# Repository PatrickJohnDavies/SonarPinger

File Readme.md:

# Intro
FPGA based single channel sonar.

# Release Notes:
* V0

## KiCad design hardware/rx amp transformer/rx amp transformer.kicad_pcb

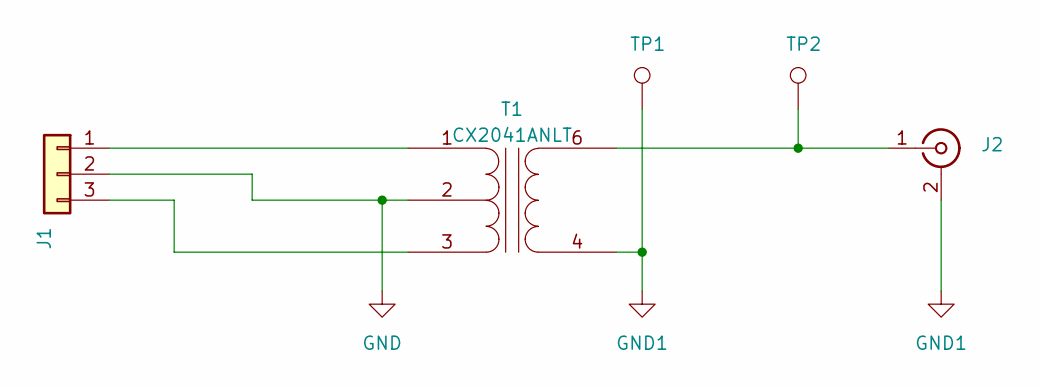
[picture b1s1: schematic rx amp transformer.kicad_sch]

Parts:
J1: Conn_01x03; PinHeader_1x03_P2.54mm_Vertical
J2: Conn_Coaxial; BNC_Molex_0731000105_Horizontal
T1: CX2041ANLT
TP1, TP2: TestPoint; TestPoint_THTPad_D1.8mm_Drill1.2mm

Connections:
GND: J1.2, T1.2 (SC)
GND1: J2.2 (Ext), T1.4 (AA), TP1.1
unnamed: J1.1, T1.1 (SA)
unnamed: J1.3, T1.3 (SB)
unnamed: J2.1 (In), T1.6 (AB), TP2.1

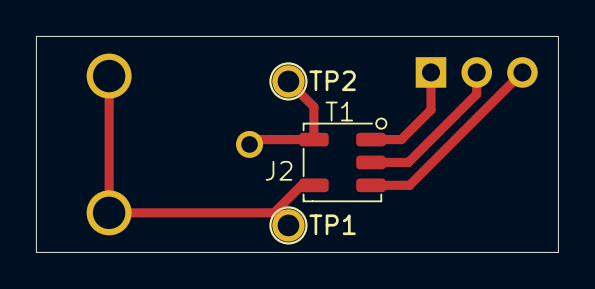
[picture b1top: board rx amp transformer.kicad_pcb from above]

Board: 2 copper layers, 29.0 x 12.0 mm, 5 parts (1 on the bottom side), 5 nets.

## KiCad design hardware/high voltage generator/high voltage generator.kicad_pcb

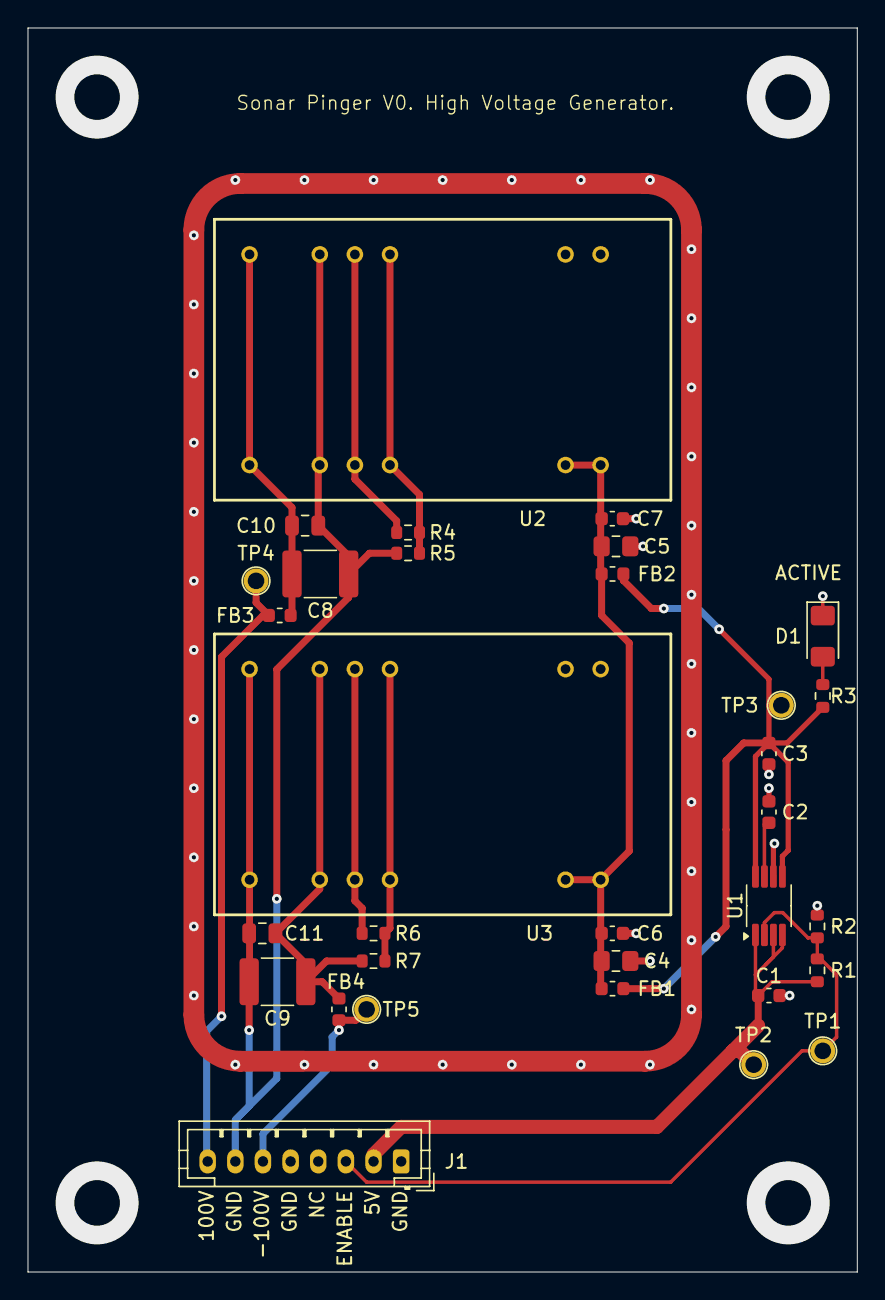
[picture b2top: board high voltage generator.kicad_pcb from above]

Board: 2 copper layers, 60.0 x 90.0 mm, 34 parts (1 on the bottom side), 16 nets.

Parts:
C1, C3, C6, C7: 0.1u; C_0603_1608Metric
C2: 1n; C_0603_1608Metric
C4, C5: 10u; C_0805_2012Metric_Pad1.18x1.45mm_HandSolder
C8, C9: 1u; C_1812_4532Metric
C10, C11: 10n; C_0805_2012Metric
D1: LED; LED_1206_3216Metric_Pad1.42x1.75mm_HandSolder
FB1, FB2, FB3, FB4: FerriteBead; L_0603_1608Metric
J1: Conn_01x08; JST_PH_B8B-PH-K_1x08_P2.00mm_Vertical
J2: RFShield_TwoPieces; Shield_MS638-10F
NT1: NetTie_2; NetTie-2_SMD_Pad0.5mm
R1, R2: 10K; R_0603_1608Metric
R3: 120; R_0603_1608Metric
R4, R6: 1.5k; R_0603_1608Metric
R5, R7: 3.6k; R_0603_1608Metric
TP1, TP2, TP3, TP4, TP5: TestPoint; TestPoint_THTPad_D1.8mm_Drill1.2mm
U1: TPS22958; VSSOP-8_3x3mm_P0.65mm
U2, U3: R05-100B; Converter_DCDC_RECOM_RXX-B

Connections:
+5V: C1.1, J1.2, R1.2, TP2.1, U1.1 (VIN), U1.3 (VBIAS), U1.4 (VIN)
+VIN: C4.1, C5.1, C6.1, C7.1, FB1.2, FB2.2, U2.22 (+VIN), U2.23 (+VIN), U3.22 (+VIN), U3.23 (+VIN)
/100V: FB3.2, J1.8, TP4.1
/+VO: C8.2, C10.2, FB3.1, U2.12 (+VOUT), U2.13 (+VOUT)
/-100V: FB4.2, J1.6, TP5.1
/-VO: C9.1, C11.1, FB4.1, R7.2, U3.10 (-VOUT), U3.15 (-VOUT)
/ENABLE: J1.3, R1.1, R2.2, TP1.1, U1.2 (ON)
GND: C1.2, C2.2, C3.2, C4.2, C5.2, C6.2, C7.2, D1.1 (K), J1.1, J1.5, J1.7, J2.1 (Shield), NT1.1, R2.1, U1.6 (GND), U2.2 (-VIN), U2.3 (-VIN), U3.2 (-VIN), U3.3 (-VIN)
GND1: C8.1, C9.2, C10.1, C11.2, NT1.2, R5.2, U2.10 (-VOUT), U2.15 (-VOUT), U3.12 (+VOUT), U3.13 (+VOUT)
unnamed: D1.2 (A), R3.1
unnamed: R4.1, U2.9 (VREF), U2.16 (VREF)
unnamed: R4.2, R5.1, U2.8 (VADJ), U2.17 (VADJ)
unnamed: R6.1, U3.9 (VREF), U3.16 (VREF)
unnamed: R6.2, R7.1, U3.8 (VADJ), U3.17 (VADJ)
unnamed: C2.1, U1.7 (CT)
VDC: C3.1, FB1.1, FB2.1, R3.2, TP3.1, U1.5 (VOUT), U1.8 (VOUT)

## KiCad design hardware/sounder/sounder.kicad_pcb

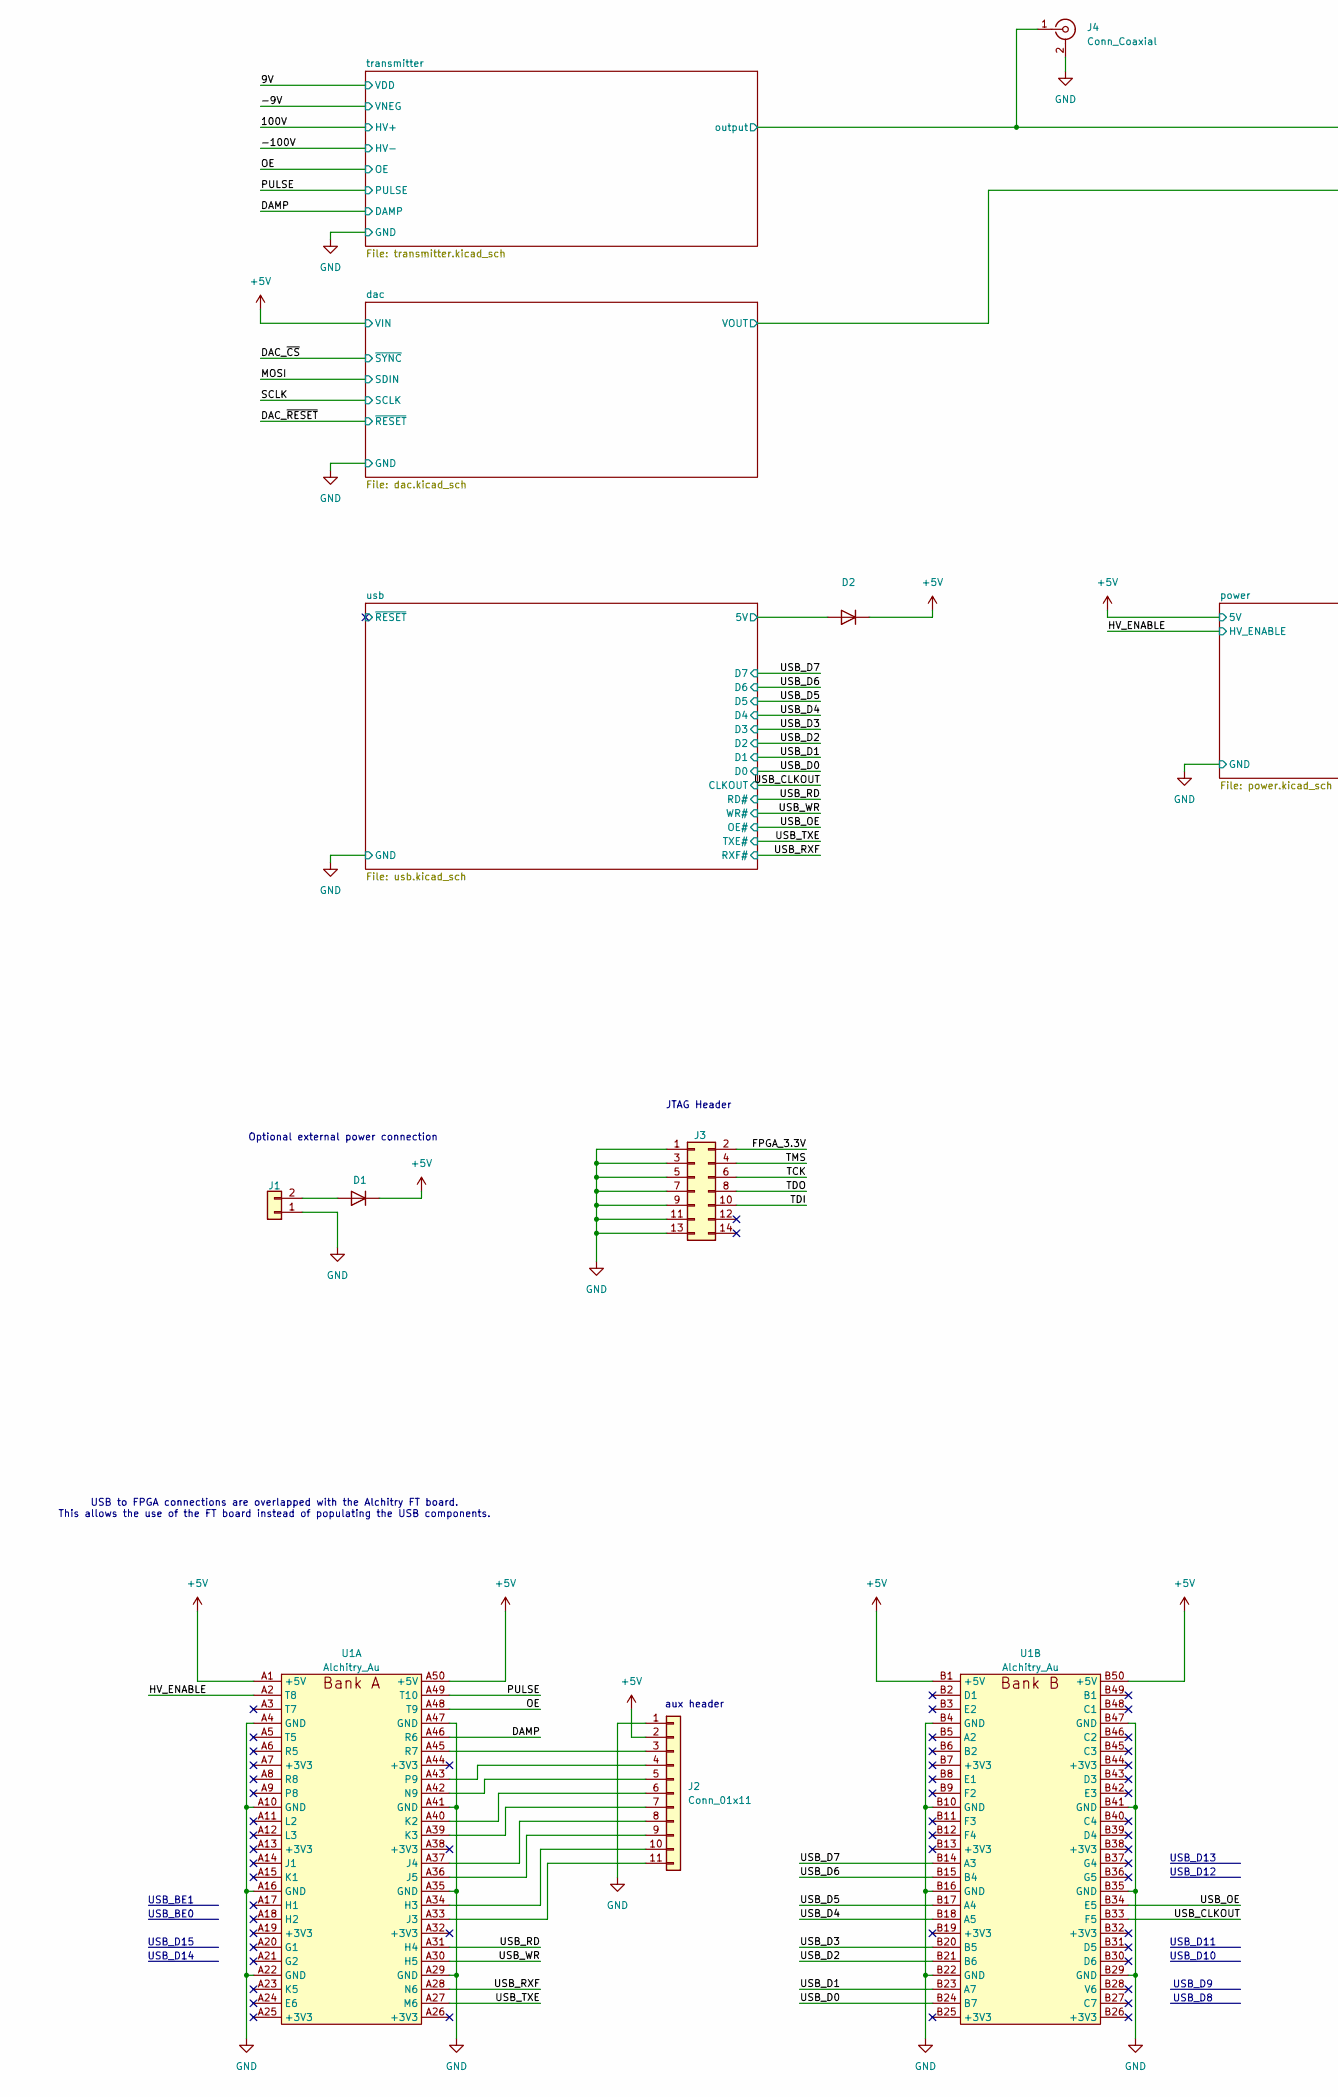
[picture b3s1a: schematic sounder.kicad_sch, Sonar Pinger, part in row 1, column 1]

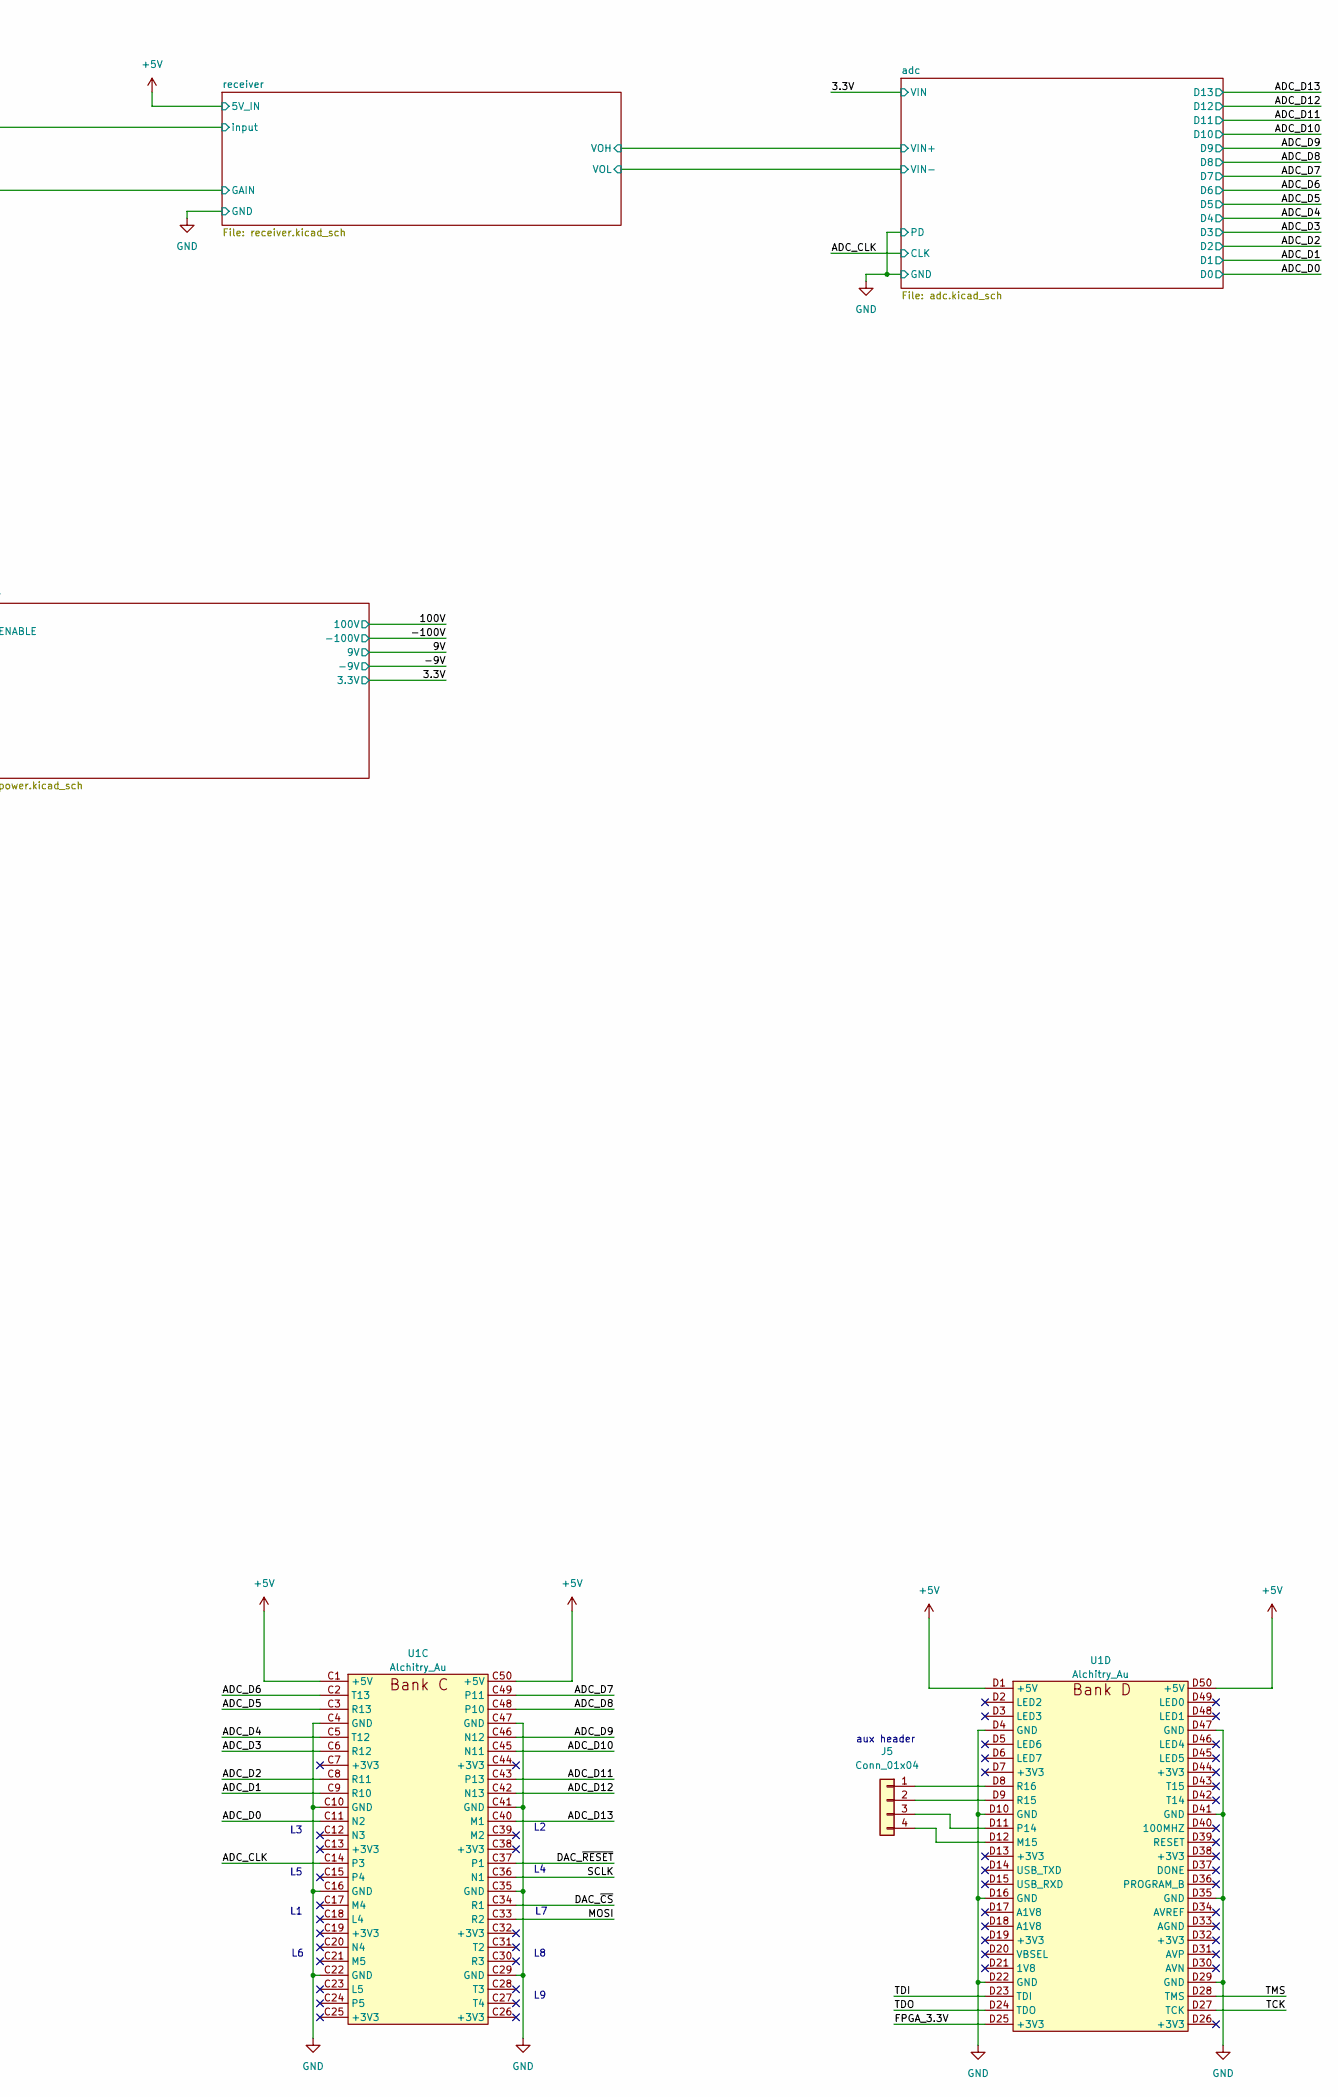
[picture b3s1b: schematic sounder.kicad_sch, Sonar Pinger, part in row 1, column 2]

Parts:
D1, D2: D; D_SOD-123F
J1: Conn_01x02; JST_PH_B2B-PH-K_1x02_P2.00mm_Vertical
J2: Conn_01x11; PinHeader_1x11_P2.54mm_Vertical
J3: Conn_02x07_Odd_Even; PinHeader_2x07_P2.54mm_Vertical
J4: Conn_Coaxial; RF2-04A-T-00-50-G
J5: Conn_01x04; PinHeader_1x04_P2.54mm_Vertical
U1: Alchitry_Au

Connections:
+5V: D1.1 (K), D2.1 (K), J2.2, U1.A1 (+5V), U1.A50 (+5V), U1.B1 (+5V), U1.B50 (+5V), U1.C1 (+5V), U1.C50 (+5V), U1.D1 (+5V), U1.D50 (+5V); also elsewhere on the board
/ADC_CLK: U1.C14 (P3); also elsewhere on the board
/ADC_D0: U1.C11 (N2); also elsewhere on the board
/ADC_D1: U1.C9 (R10); also elsewhere on the board
/ADC_D2: U1.C8 (R11); also elsewhere on the board
/ADC_D3: U1.C6 (R12); also elsewhere on the board
/ADC_D4: U1.C5 (T12); also elsewhere on the board
/ADC_D5: U1.C3 (R13); also elsewhere on the board
/ADC_D6: U1.C2 (T13); also elsewhere on the board
/ADC_D7: U1.C49 (P11); also elsewhere on the board
/ADC_D8: U1.C48 (P10); also elsewhere on the board
/ADC_D9: U1.C46 (N12); also elsewhere on the board
/ADC_D10: U1.C45 (N11); also elsewhere on the board
/ADC_D11: U1.C43 (P13); also elsewhere on the board
/ADC_D12: U1.C42 (N13); also elsewhere on the board
/ADC_D13: U1.C40 (M1); also elsewhere on the board
/DAC_~CS: U1.C34 (R1); also elsewhere on the board
/DAC_~RESET: U1.C37 (P1); also elsewhere on the board
/DAMP: U1.A46 (R6); also elsewhere on the board
/FPGA_3.3V: J3.2, U1.D25 (+3V3)
/HV_ENABLE: U1.A2 (T8); also elsewhere on the board
/MOSI: U1.C33 (R2); also elsewhere on the board
/OE: U1.A48 (T9); also elsewhere on the board
/PULSE: U1.A49 (T10); also elsewhere on the board
/SCLK: U1.C36 (N1); also elsewhere on the board
/TCK: J3.6, U1.D27 (TCK)
/TDI: J3.10, U1.D23 (TDI)
/TDO: J3.8, U1.D24 (TDO)
/TMS: J3.4, U1.D28 (TMS)
/USB_CLKOUT: U1.B33 (F5); also elsewhere on the board
/USB_D0: U1.B24 (B7); also elsewhere on the board
/USB_D1: U1.B23 (A7); also elsewhere on the board
/USB_D2: U1.B21 (B6); also elsewhere on the board
/USB_D3: U1.B20 (B5); also elsewhere on the board
/USB_D4: U1.B18 (A5); also elsewhere on the board
/USB_D5: U1.B17 (A4); also elsewhere on the board
/USB_D6: U1.B15 (B4); also elsewhere on the board
/USB_D7: U1.B14 (A3); also elsewhere on the board
/USB_OE: U1.B34 (E5); also elsewhere on the board
/USB_RD: U1.A31 (H4); also elsewhere on the board
/USB_RXF: U1.A28 (N6); also elsewhere on the board
/USB_TXE: U1.A27 (M6); also elsewhere on the board
/USB_WR: U1.A30 (H5); also elsewhere on the board
/receiver/input: J4.1 (In); also elsewhere on the board
/usb/5V: D2.2 (A); also elsewhere on the board
GND: J1.1, J2.1, J3.1, J3.3, J3.5, J3.7, J3.9, J3.11, J3.13, J4.2 (Ext), U1.A4 (GND), U1.A10 (GND), U1.A16 (GND), U1.A22 (GND), U1.A29 (GND), U1.A35 (GND), U1.A41 (GND), U1.A47 (GND), U1.B4 (GND), U1.B10 (GND), U1.B16 (GND), U1.B22 (GND), U1.B29 (GND), U1.B35 (GND), U1.B41 (GND), U1.B47 (GND), U1.C4 (GND), U1.C10 (GND), U1.C16 (GND), U1.C22 (GND), U1.C29 (GND), U1.C35 (GND), U1.C41 (GND), U1.C47 (GND), U1.D4 (GND), U1.D10 (GND), U1.D16 (GND), U1.D22 (GND), U1.D29 (GND), U1.D35 (GND), U1.D41 (GND), U1.D47 (GND); also elsewhere on the board
unnamed: D1.2 (A), J1.2
unnamed: J2.3, U1.A45 (R7)
unnamed: J2.4, U1.A43 (P9)
unnamed: J2.5, U1.A42 (N9)
unnamed: J2.6, U1.A40 (K2)
unnamed: J2.7, U1.A39 (K3)
unnamed: J2.8, U1.A37 (J4)
unnamed: J2.9, U1.A36 (J5)
unnamed: J2.10, U1.A34 (H3)
unnamed: J2.11, U1.A33 (J3)
unnamed: J5.1, U1.D8 (R16)
unnamed: J5.2, U1.D9 (R15)
unnamed: J5.3, U1.D11 (P14)
unnamed: J5.4, U1.D12 (M15)

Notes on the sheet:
Optional external power connection
USB_D12
JTAG Header
USB_BE1
aux header
USB_D15
USB_D10
USB_D8
USB to FPGA connections are overlapped with the Alchitry FT board. This allows the use of the FT board instead of populating the USB components.
USB_BE0
USB_D13
USB_D9
USB_D14
USB_D11

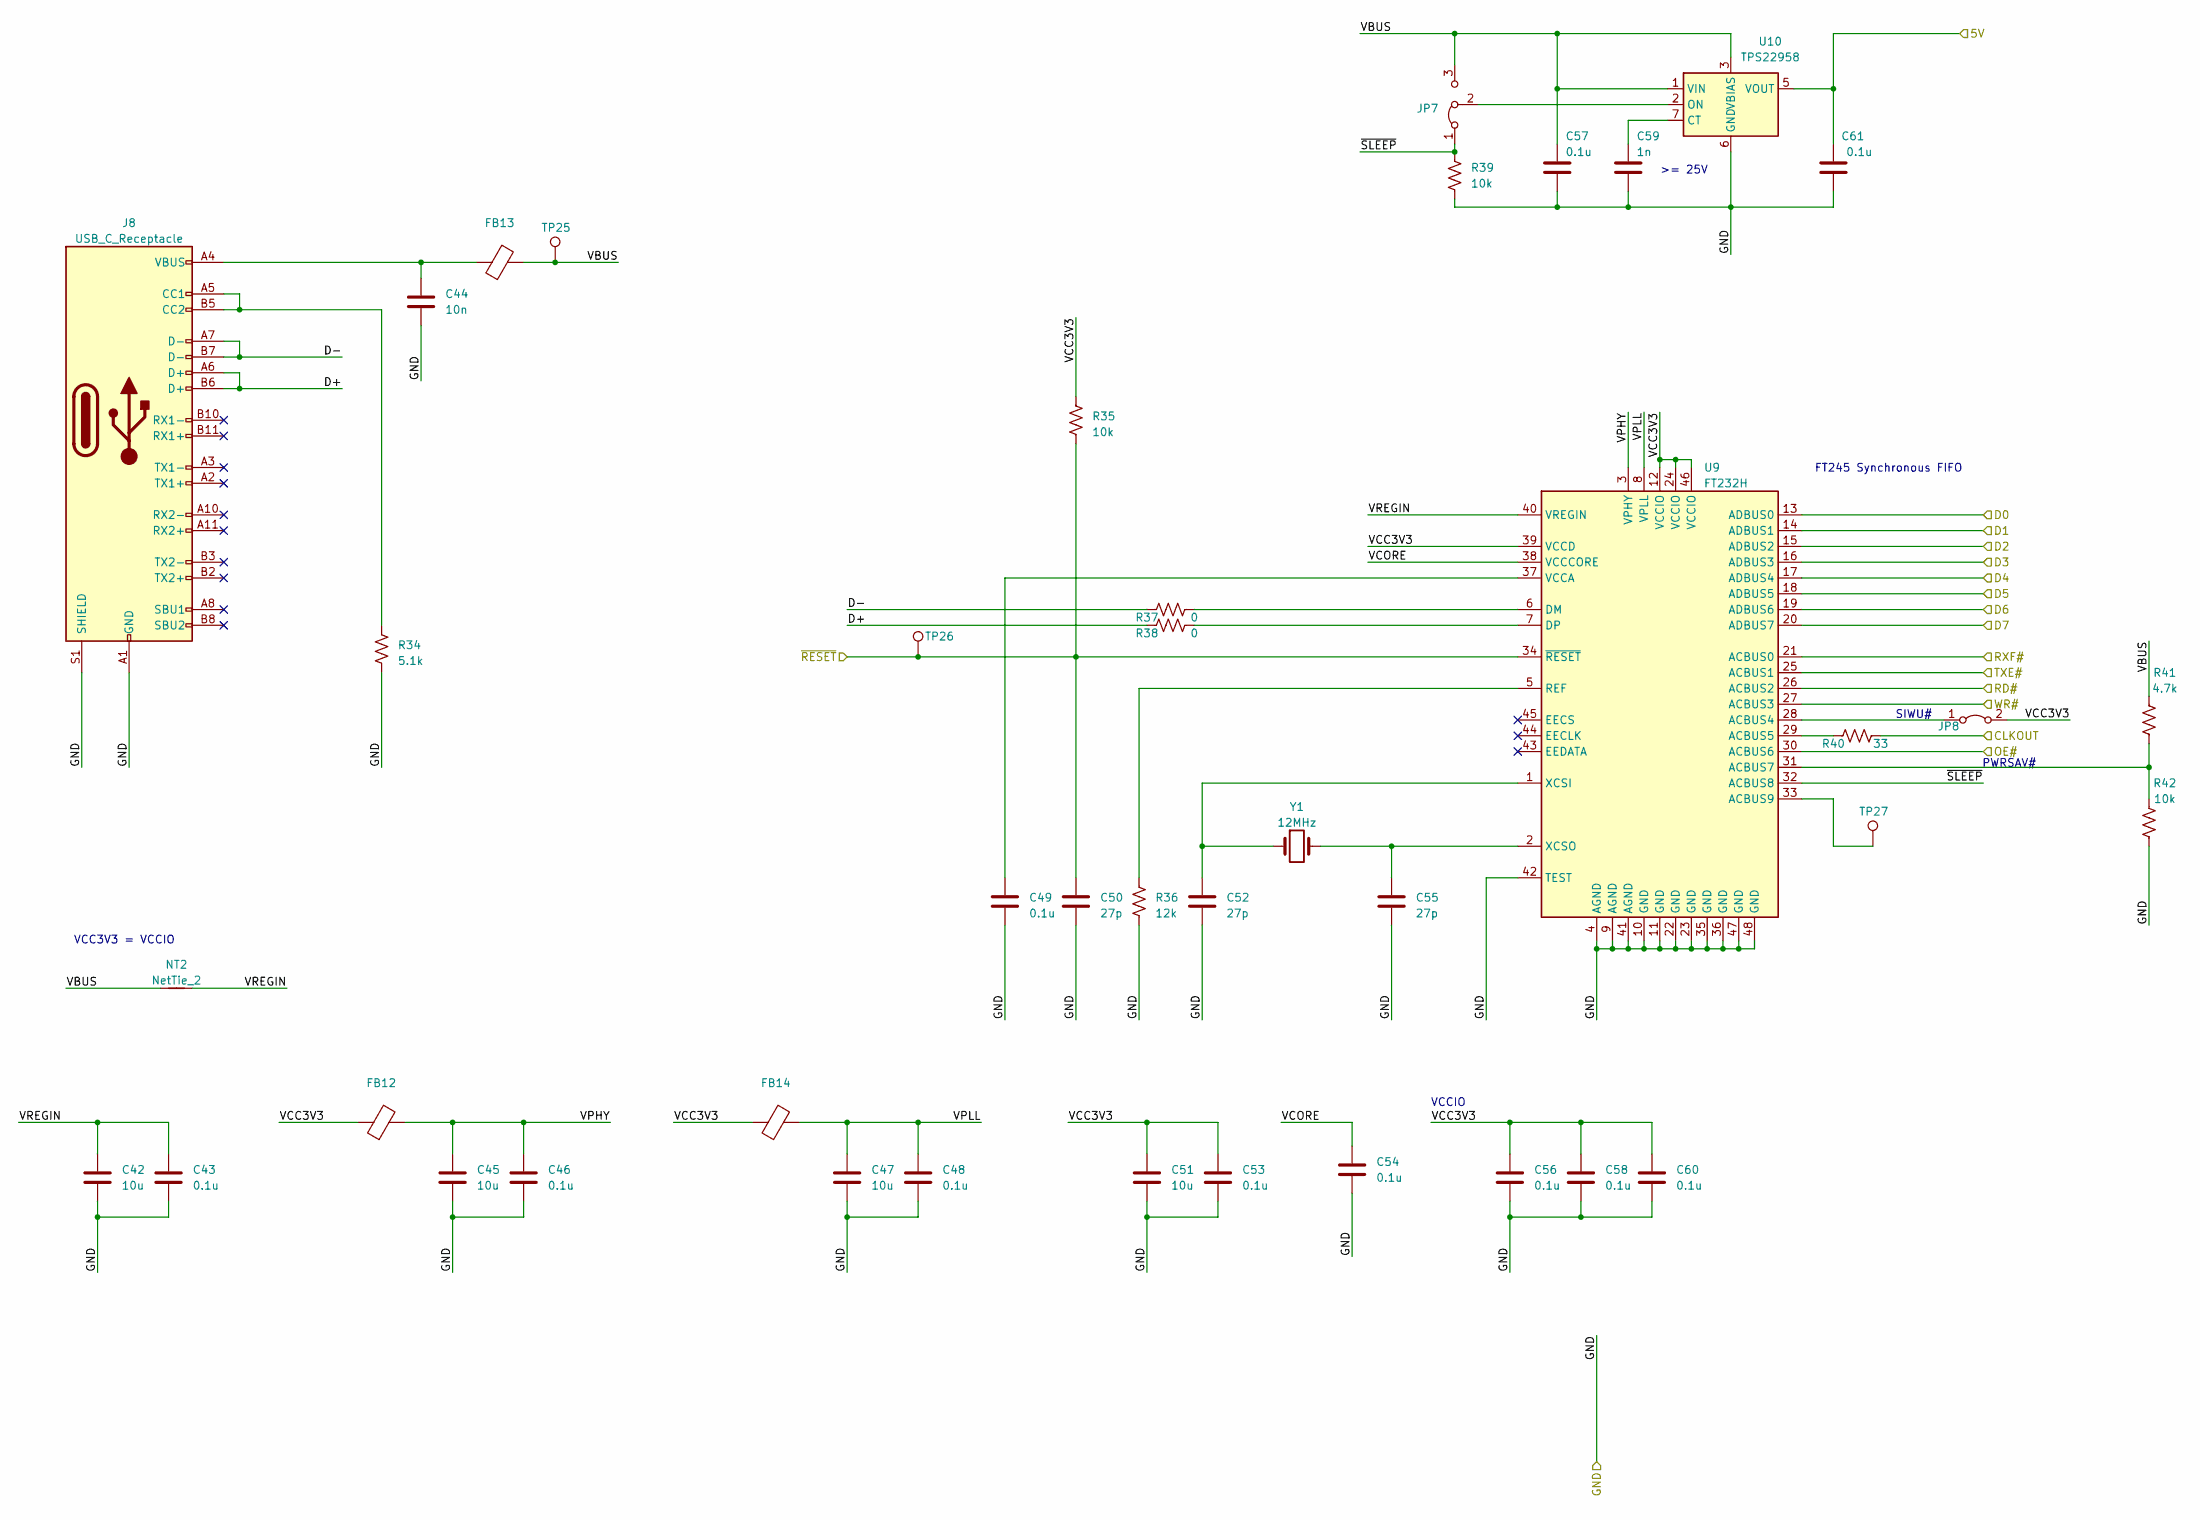
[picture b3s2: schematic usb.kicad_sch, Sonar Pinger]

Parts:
C42, C45, C47, C51: 10u; C_0805_2012Metric_Pad1.18x1.45mm_HandSolder
C43, C46, C48, C49, C53, C54, C56, C57, C58, C60, C61: 0.1u; C_0603_1608Metric
C44: 10n; C_0603_1608Metric
C50, C52, C55: 27p; C_0603_1608Metric
C59: 1n; C_0603_1608Metric
FB12, FB13, FB14: FerriteBead; L_0603_1608Metric
J8: USB_C_Receptacle; USB_C_Receptacle_Amphenol_12401548E4-2A_CircularHoles
JP7: Jumper_3_Bridged12; SolderJumper-3_P1.3mm_Bridged12_RoundedPad1.0x1.5mm
JP8: Jumper_2_Bridged; SolderJumper-2_P1.3mm_Bridged_RoundedPad1.0x1.5mm
NT2: NetTie_2; NetTie-2_SMD_Pad0.5mm
R34: 5.1k; R_0603_1608Metric
R35, R39, R42: 10k; R_0603_1608Metric
R36: 12k; R_0603_1608Metric
R37, R38: 0; R_0603_1608Metric
R40: 33; R_0603_1608Metric
R41: 4.7k; R_0603_1608Metric
TP25, TP26, TP27: TestPoint; TestPoint_THTPad_D1.8mm_Drill1.2mm
U9: FT232H; LQFP-48_7x7mm_P0.5mm
U10: TPS22958; VSSOP-8_3x3mm_P0.65mm
Y1: 12MHz; Crystal_SMD_HC49-SD_HandSoldering

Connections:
/USB_CLKOUT: R40.2; also elsewhere on the board
/USB_D0: U9.13 (ADBUS0); also elsewhere on the board
/USB_D1: U9.14 (ADBUS1); also elsewhere on the board
/USB_D2: U9.15 (ADBUS2); also elsewhere on the board
/USB_D3: U9.16 (ADBUS3); also elsewhere on the board
/USB_D4: U9.17 (ADBUS4); also elsewhere on the board
/USB_D5: U9.18 (ADBUS5); also elsewhere on the board
/USB_D6: U9.19 (ADBUS6); also elsewhere on the board
/USB_D7: U9.20 (ADBUS7); also elsewhere on the board
/USB_OE: U9.30 (ACBUS6); also elsewhere on the board
/USB_RD: U9.26 (ACBUS2); also elsewhere on the board
/USB_RXF: U9.21 (ACBUS0); also elsewhere on the board
/USB_TXE: U9.25 (ACBUS1); also elsewhere on the board
/USB_WR: U9.27 (ACBUS3); also elsewhere on the board
/usb/5V: C61.1, U10.5 (VOUT), U10.8 (VOUT); also elsewhere on the board
/usb/D+: J8.A6 (D+), J8.B6 (D+), R38.1
/usb/D-: J8.A7 (D-), J8.B7 (D-), R37.1
/usb/VCC3V3: C51.1, C53.1, C56.1, C58.1, C60.1, FB12.1, FB14.1, JP8.2 (B), R35.1, U9.12 (VCCIO), U9.24 (VCCIO), U9.39 (VCCD), U9.46 (VCCIO)
/usb/VCORE: C54.1, U9.38 (VCCCORE)
/usb/VPHY: C45.1, C46.1, FB12.2, U9.3 (VPHY)
/usb/VPLL: C47.1, C48.1, FB14.2, U9.8 (VPLL)
/usb/VREGIN: C42.1, C43.1, NT2.2, U9.40 (VREGIN)
/usb/~RESET: C50.1, R35.2, TP26.1, U9.34 (~RESET)
/usb/~SLEEP: JP7.1 (A), R39.2, U9.32 (ACBUS8)
GND: C42.2, C43.2, C44.2, C45.2, C46.2, C47.2, C48.2, C49.2, C50.2, C51.2, C52.2, C53.2, C54.2, C55.2, C56.2, C57.2, C58.2, C59.2, C60.2, C61.2, J8.A1 (GND), J8.A12 (GND), J8.B1 (GND), J8.B12 (GND), J8.S1 (SHIELD), R34.2, R36.2, R39.1, R42.1, U9.4 (AGND), U9.9 (AGND), U9.10 (GND), U9.11 (GND), U9.22 (GND), U9.23 (GND), U9.35 (GND), U9.36 (GND), U9.41 (AGND), U9.42 (TEST), U9.47 (GND), U9.48 (GND), U10.6 (GND); also elsewhere on the board
unnamed: C44.1, FB13.1, J8.A4 (VBUS), J8.A9 (VBUS), J8.B4 (VBUS), J8.B9 (VBUS)
unnamed: J8.A5 (CC1), J8.B5 (CC2), R34.1
unnamed: JP7.2 (C), U10.2 (ON)
unnamed: JP8.1 (A), U9.28 (ACBUS4)
unnamed: R40.1, U9.29 (ACBUS5)
unnamed: R41.1, R42.2, U9.31 (ACBUS7)
unnamed: TP27.1, U9.33 (ACBUS9)
unnamed: R37.2, U9.6 (DM)
unnamed: R38.2, U9.7 (DP)
unnamed: R36.1, U9.5 (REF)
unnamed: C49.1, U9.37 (VCCA)
unnamed: C52.1, U9.1 (XCSI), Y1.1
unnamed: C55.1, U9.2 (XCSO), Y1.2
unnamed: C59.1, U10.7 (CT)
VIN: C57.1, FB13.2, JP7.3 (B), NT2.1, R41.2, TP25.1, U10.1 (VIN), U10.3 (VBIAS), U10.4 (VIN)

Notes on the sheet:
VCCIO
VCC3V3 = VCCIO
>= 25V
FT245 Synchronous FIFO
PWRSAV#
SIWU#

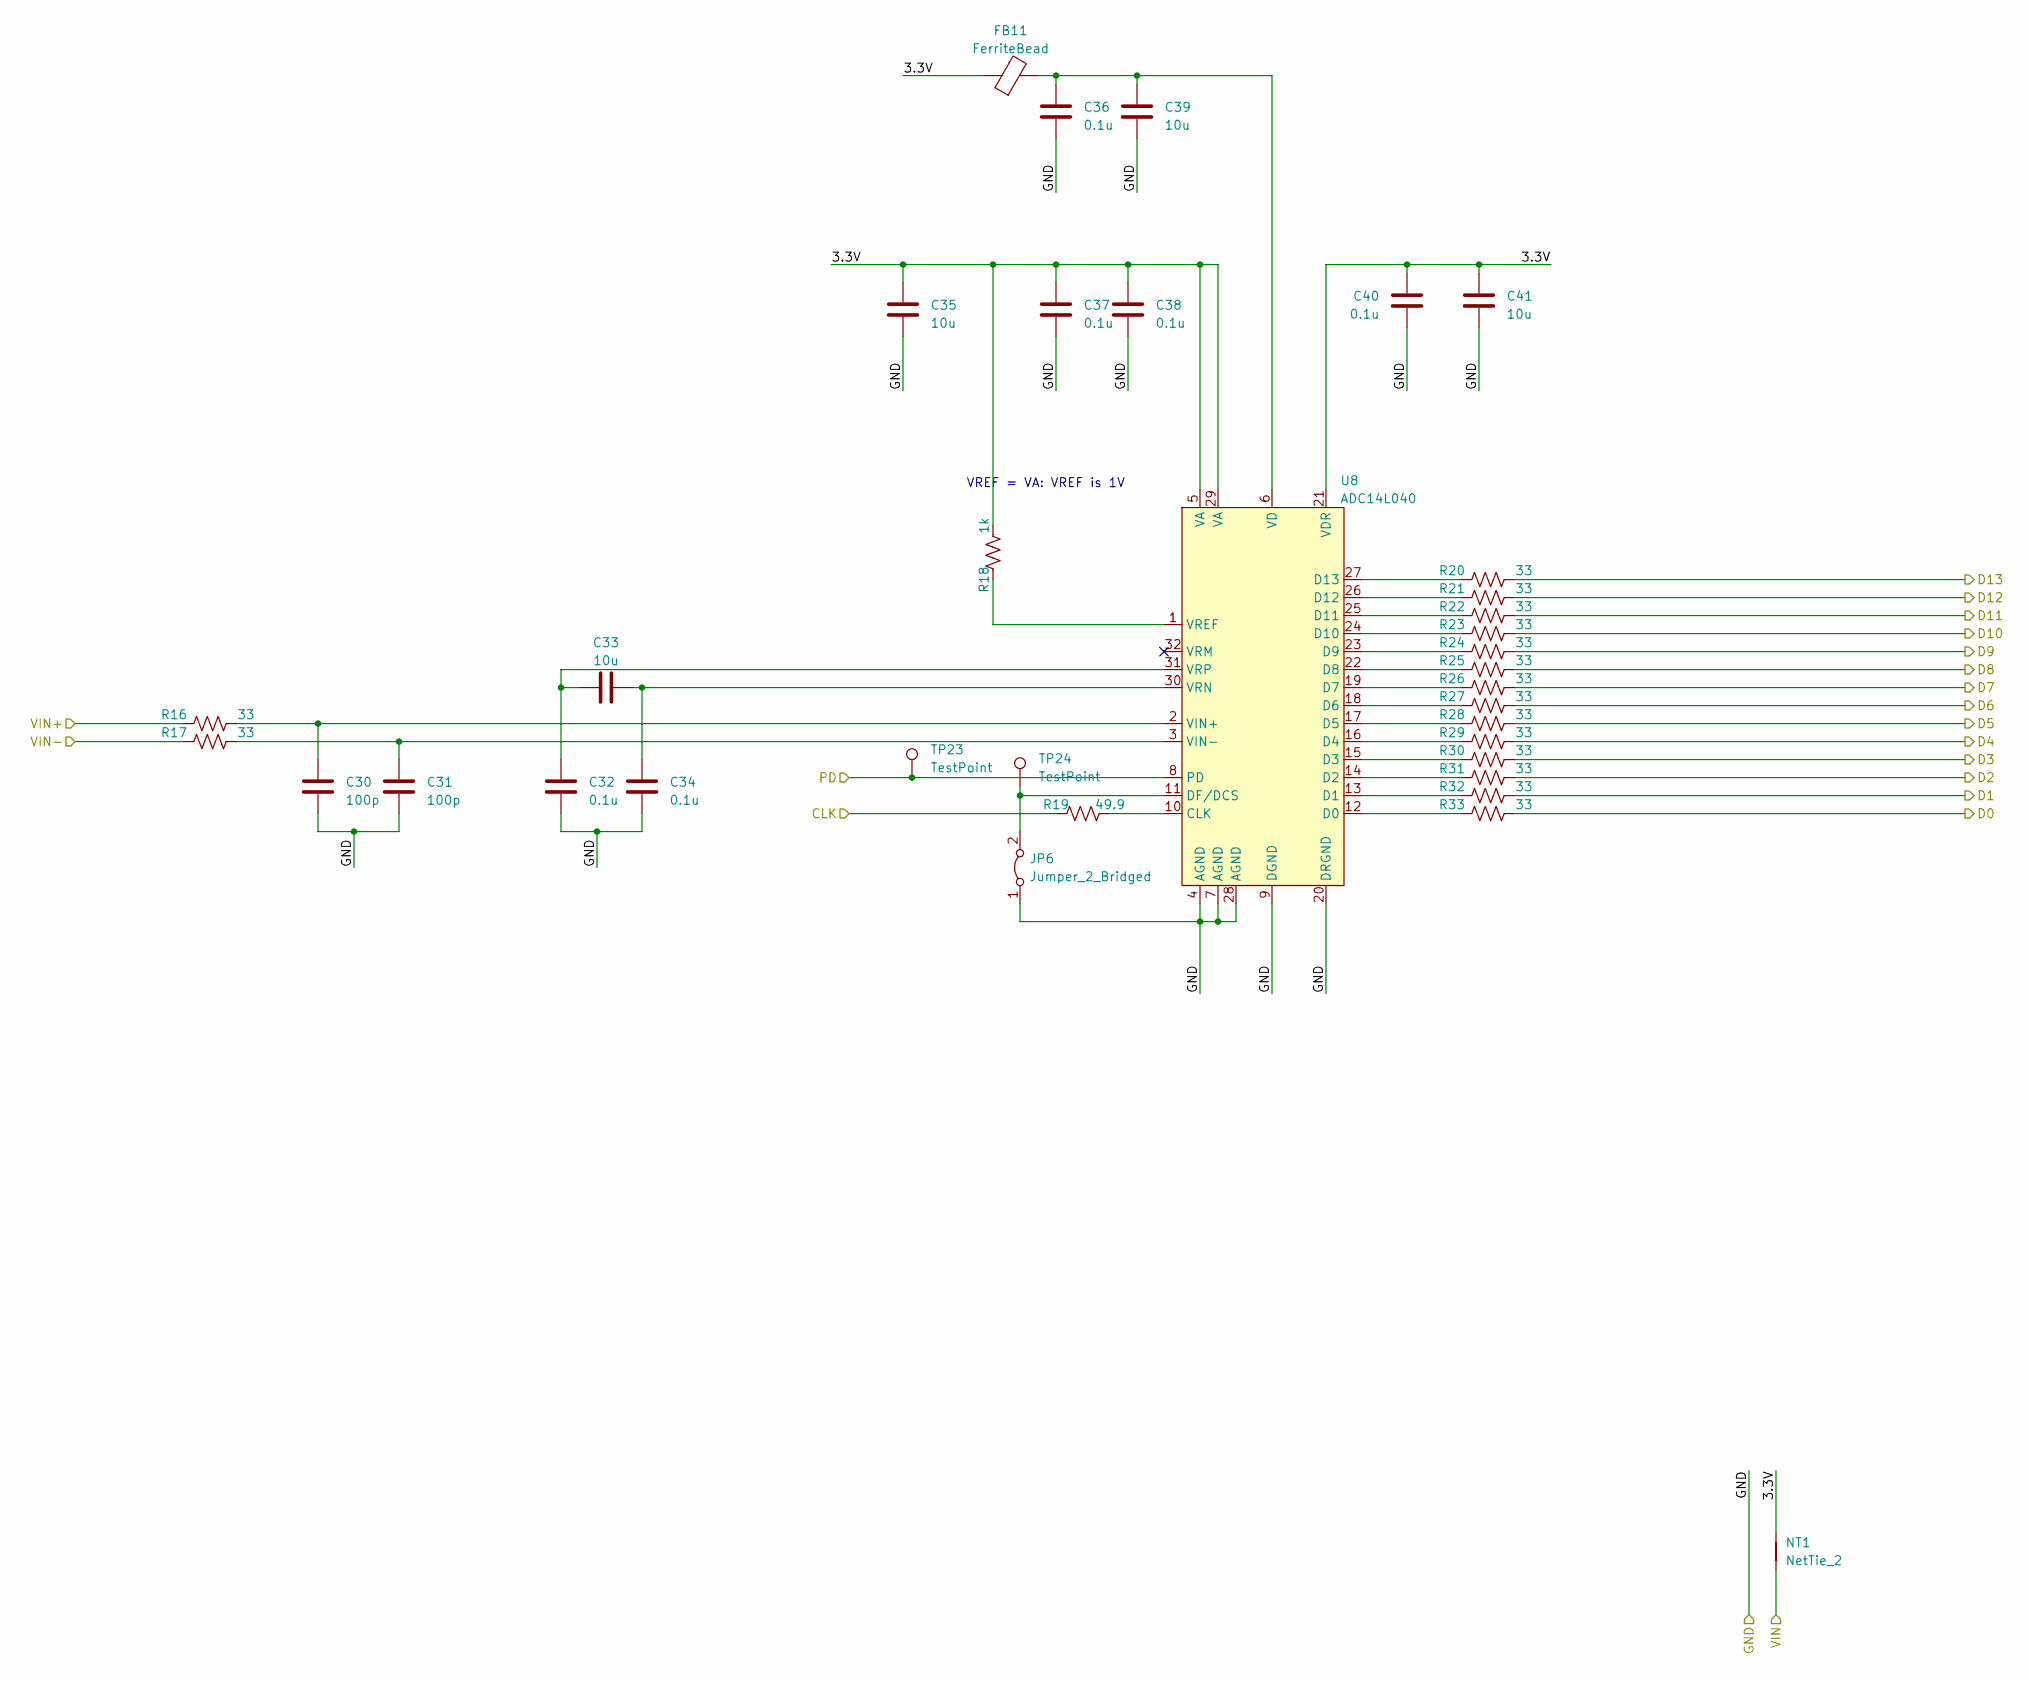
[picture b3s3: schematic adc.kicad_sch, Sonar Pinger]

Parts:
C30, C31: 100p; C_0603_1608Metric
C32, C34, C36, C37, C38, C40: 0.1u; C_0603_1608Metric
C33, C35, C39, C41: 10u; C_0805_2012Metric_Pad1.18x1.45mm_HandSolder
FB11: FerriteBead; L_0603_1608Metric
JP6: Jumper_2_Bridged; SolderJumper-2_P1.3mm_Bridged_RoundedPad1.0x1.5mm
NT1: NetTie_2; NetTie-2_SMD_Pad0.5mm
R16, R17, R20, R21, R22, R23, R24, R25, R26, R27, R28, R29, R30, R31, R32, R33: 33; R_0603_1608Metric
R18: 1k; R_0603_1608Metric
R19: 49.9; R_0603_1608Metric
TP23, TP24: TestPoint; TestPoint_THTPad_D1.8mm_Drill1.2mm
U8: ADC14L040; LQFP-32_7x7mm_P0.8mm

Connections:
/3.3V: NT1.1; also elsewhere on the board
/ADC_CLK: R19.1; also elsewhere on the board
/ADC_D0: R33.2; also elsewhere on the board
/ADC_D1: R32.2; also elsewhere on the board
/ADC_D2: R31.2; also elsewhere on the board
/ADC_D3: R30.2; also elsewhere on the board
/ADC_D4: R29.2; also elsewhere on the board
/ADC_D5: R28.2; also elsewhere on the board
/ADC_D6: R27.2; also elsewhere on the board
/ADC_D7: R26.2; also elsewhere on the board
/ADC_D8: R25.2; also elsewhere on the board
/ADC_D9: R24.2; also elsewhere on the board
/ADC_D10: R23.2; also elsewhere on the board
/ADC_D11: R22.2; also elsewhere on the board
/ADC_D12: R21.2; also elsewhere on the board
/ADC_D13: R20.2; also elsewhere on the board
/adc/3.3V: C35.1, C37.1, C38.1, C40.1, C41.1, FB11.1, NT1.2, R18.2, U8.5 (VA), U8.21 (VDR), U8.29 (VA)
/adc/VIN+: R16.1; also elsewhere on the board
/adc/VIN-: R17.1; also elsewhere on the board
GND: C30.2, C31.2, C32.2, C34.2, C35.2, C36.2, C37.2, C38.2, C39.2, C40.2, C41.2, JP6.1 (A), TP23.1, U8.4 (AGND), U8.7 (AGND), U8.8 (PD), U8.9 (DGND), U8.20 (DRGND), U8.28 (AGND); also elsewhere on the board
unnamed: JP6.2 (B), TP24.1, U8.11 (DF/DCS)
unnamed: R19.2, U8.10 (CLK)
unnamed: R33.1, U8.12 (D0)
unnamed: R32.1, U8.13 (D1)
unnamed: R31.1, U8.14 (D2)
unnamed: R30.1, U8.15 (D3)
unnamed: R29.1, U8.16 (D4)
unnamed: R28.1, U8.17 (D5)
unnamed: R27.1, U8.18 (D6)
unnamed: R26.1, U8.19 (D7)
unnamed: R25.1, U8.22 (D8)
unnamed: R24.1, U8.23 (D9)
unnamed: R23.1, U8.24 (D10)
unnamed: R22.1, U8.25 (D11)
unnamed: R21.1, U8.26 (D12)
unnamed: R20.1, U8.27 (D13)
unnamed: C36.1, C39.1, FB11.2, U8.6 (VD)
unnamed: C30.1, R16.2, U8.2 (VIN+)
unnamed: C31.1, R17.2, U8.3 (VIN-)
unnamed: R18.1, U8.1 (VREF)
unnamed: C33.2, C34.1, U8.30 (VRN)
unnamed: C32.1, C33.1, U8.31 (VRP)

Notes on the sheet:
VREF = VA: VREF is 1V
